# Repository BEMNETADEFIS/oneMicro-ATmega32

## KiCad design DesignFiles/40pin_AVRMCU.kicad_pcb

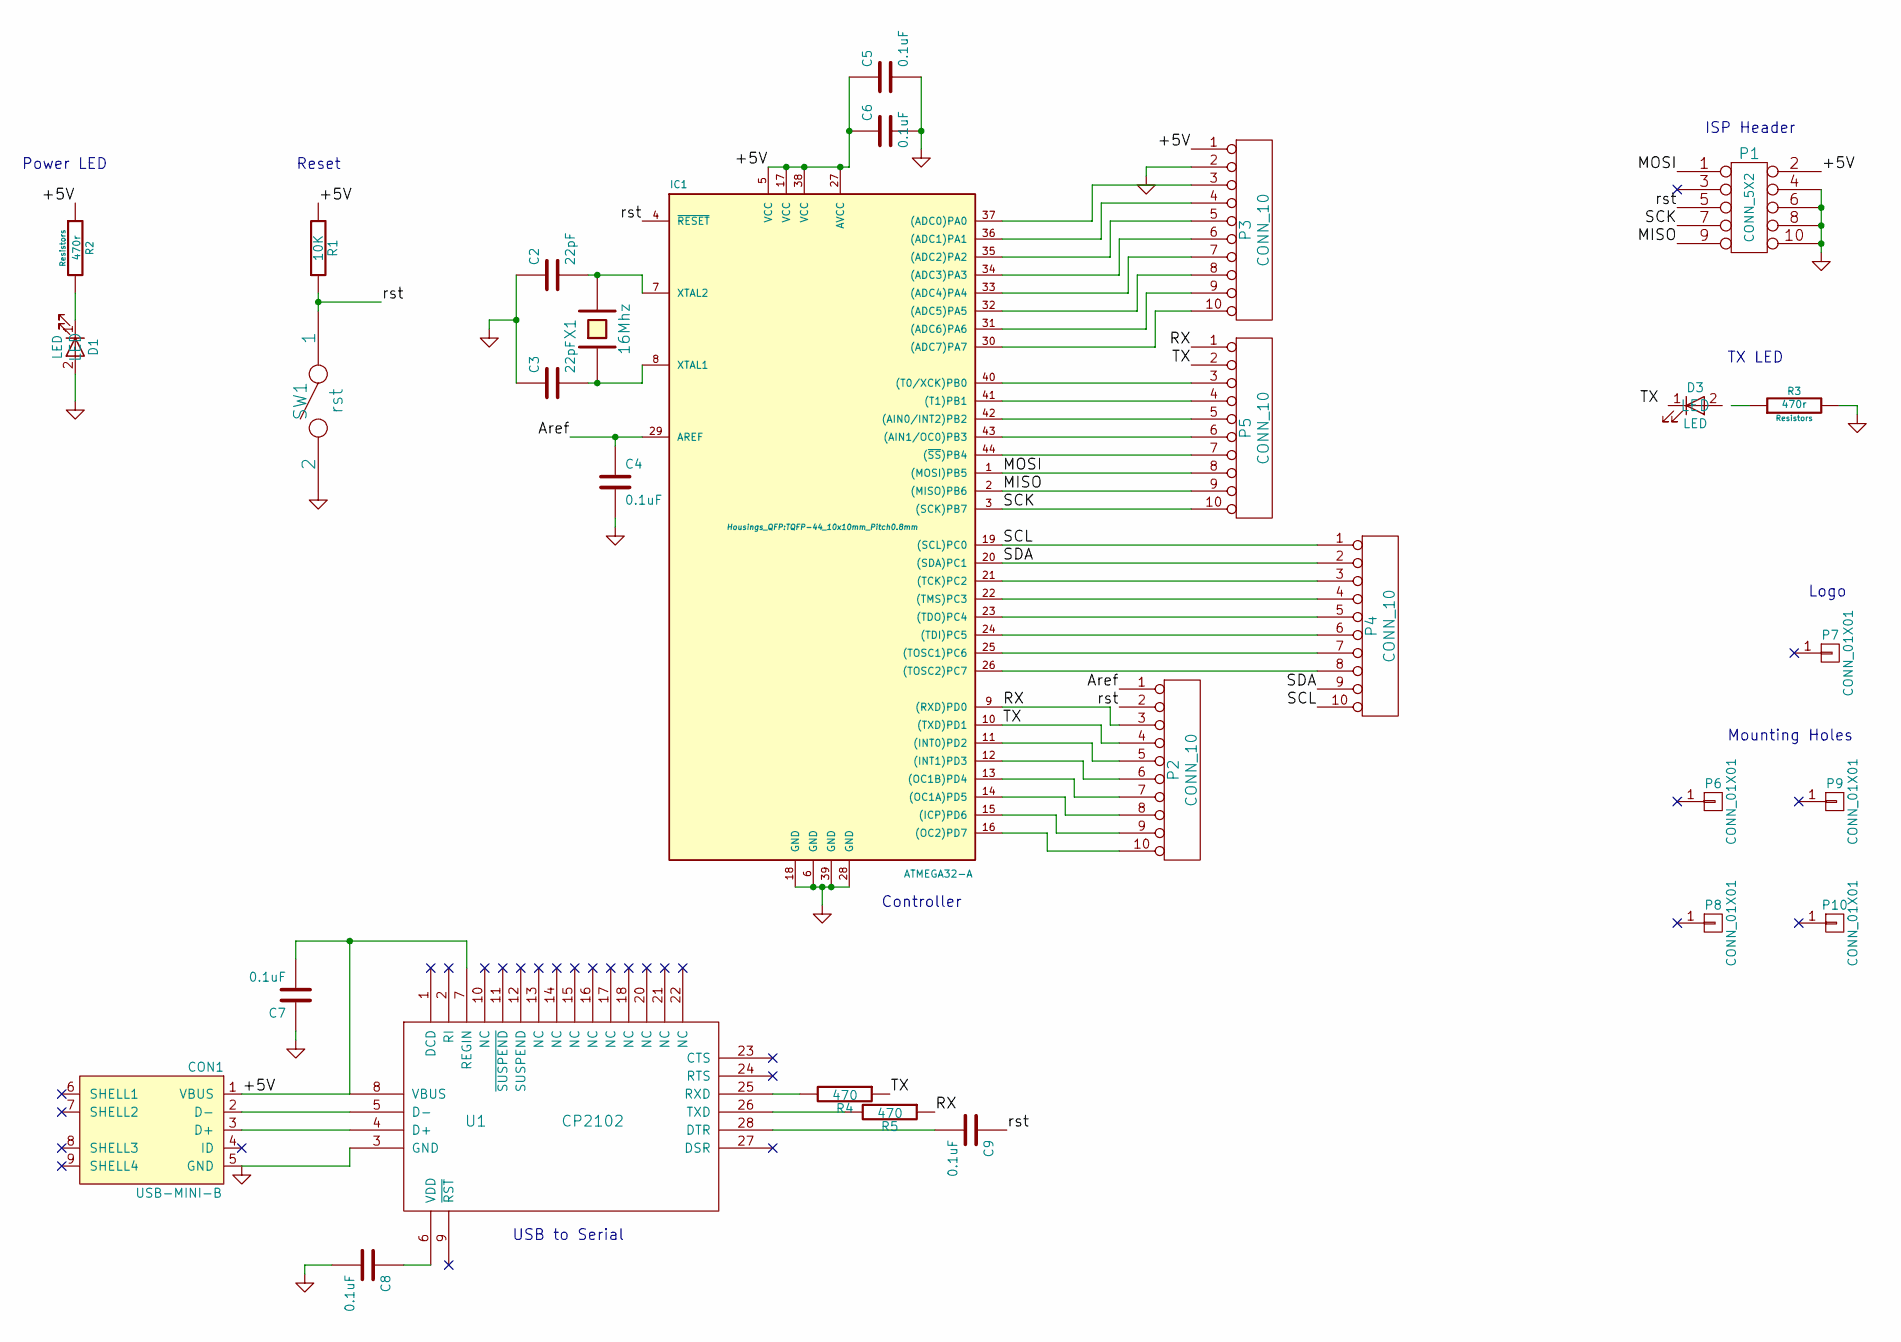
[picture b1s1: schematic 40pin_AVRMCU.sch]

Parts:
C2, C3: 22pF; C_0603_HandSoldering
C4, C5, C6, C7, C8, C9: 0.1uF; C_0603_HandSoldering
CON1: USB-MINI-B; USB_Micro-B_SMD_NEW_1
D1, D3: LED
IC1: ATMEGA32-A; TQFP-44_10x10mm_Pitch0.8mm
P1: CONN_5X2; Pin_Header_Straight_2x05_Pitch2.54mm
P2, P3, P4, P5: CONN_10; Pin_Header_Straight_1x10_Pitch2.54mm
P6, P8, P9, P10: CONN_01X01; 1pin
P7: CONN_01X01; Logo_8
R1: 10K; R_0603_HandSoldering
R2, R3: 470r; Resistors
R4, R5: 470; R_0603_HandSoldering
SW1: rst; SW_PUSH_SMALL_2pin_3D_xl_v1
U1: CP2102; cp2102_xl2
X1: 16Mhz; Crystal_HC18-U_Vertical

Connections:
/+5V: C5.1, C6.1, C7.2, CON1.1 (VBUS), IC1.5 (VCC), IC1.17 (VCC), IC1.27 (AVCC), IC1.38 (VCC), P1.2, P3.1, R1.2, R2.1, U1.7 (REGIN), U1.8 (VBUS)
/Aref: C4.1, IC1.29 (AREF), P2.1
/MISO: IC1.2 ((MISO)PB6), P1.9, P5.9
/MOSI: IC1.1 ((MOSI)PB5), P1.1, P5.8
/RX: IC1.9 ((RXD)PD0), P2.3, P5.1, R5.1
/SCK: IC1.3 ((SCK)PB7), P1.7, P5.10
/SCL: IC1.19 ((SCL)PC0), P4.1, P4.10
/SDA: IC1.20 ((SDA)PC1), P4.2, P4.9
/TX: D3.1 (K), IC1.10 ((TXD)PD1), P2.4, P5.2, R4.1
/rst: C9.1, IC1.4 (~RESET), P1.5, P2.2, R1.1, SW1.1
GND: C2.1, C3.1, C4.2, C5.2, C6.2, C7.1, C8.2, CON1.5 (GND), D1.2 (A), IC1.6 (GND), IC1.18 (GND), IC1.28 (GND), IC1.39 (GND), P1.4, P1.6, P1.8, P1.10, P3.2, R3.2, SW1.2, U1.3 (GND)
unnamed: C2.2, IC1.7 (XTAL2), X1.2
unnamed: C3.2, IC1.8 (XTAL1), X1.1
unnamed: C8.1, U1.6 (VDD)
unnamed: C9.2, U1.28 (DTR)
unnamed: CON1.2 (D-), U1.5 (D-)
unnamed: CON1.3 (D+), U1.4 (D+)
unnamed: D1.1 (K), R2.2
unnamed: D3.2 (A), R3.1
unnamed: IC1.11 ((INT0)PD2), P2.5
unnamed: IC1.12 ((INT1)PD3), P2.6
unnamed: IC1.13 ((OC1B)PD4), P2.7
unnamed: IC1.14 ((OC1A)PD5), P2.8
unnamed: IC1.15 ((ICP)PD6), P2.9
unnamed: IC1.16 ((OC2)PD7), P2.10
unnamed: IC1.21 ((TCK)PC2), P4.3
unnamed: IC1.22 ((TMS)PC3), P4.4
unnamed: IC1.23 ((TDO)PC4), P4.5
unnamed: IC1.24 ((TDI)PC5), P4.6
unnamed: IC1.25 ((TOSC1)PC6), P4.7
unnamed: IC1.26 ((TOSC2)PC7), P4.8
unnamed: IC1.30 ((ADC7)PA7), P3.10
unnamed: IC1.31 ((ADC6)PA6), P3.9
unnamed: IC1.32 ((ADC5)PA5), P3.8
unnamed: IC1.33 ((ADC4)PA4), P3.7
unnamed: IC1.34 ((ADC3)PA3), P3.6
unnamed: IC1.35 ((ADC2)PA2), P3.5
unnamed: IC1.36 ((ADC1)PA1), P3.4
unnamed: IC1.37 ((ADC0)PA0), P3.3
unnamed: IC1.40 ((T0/XCK)PB0), P5.3
unnamed: IC1.41 ((T1)PB1), P5.4
unnamed: IC1.42 ((AIN0/INT2)PB2), P5.5
unnamed: IC1.43 ((AIN1/OC0)PB3), P5.6
unnamed: IC1.44 ((~SS~)PB4), P5.7
unnamed: R4.2, U1.25 (RXD)
unnamed: R5.2, U1.26 (TXD)

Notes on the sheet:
ISP Header
Reset
TX LED
USB to Serial
Power LED
Logo
Mounting Holes
Controller

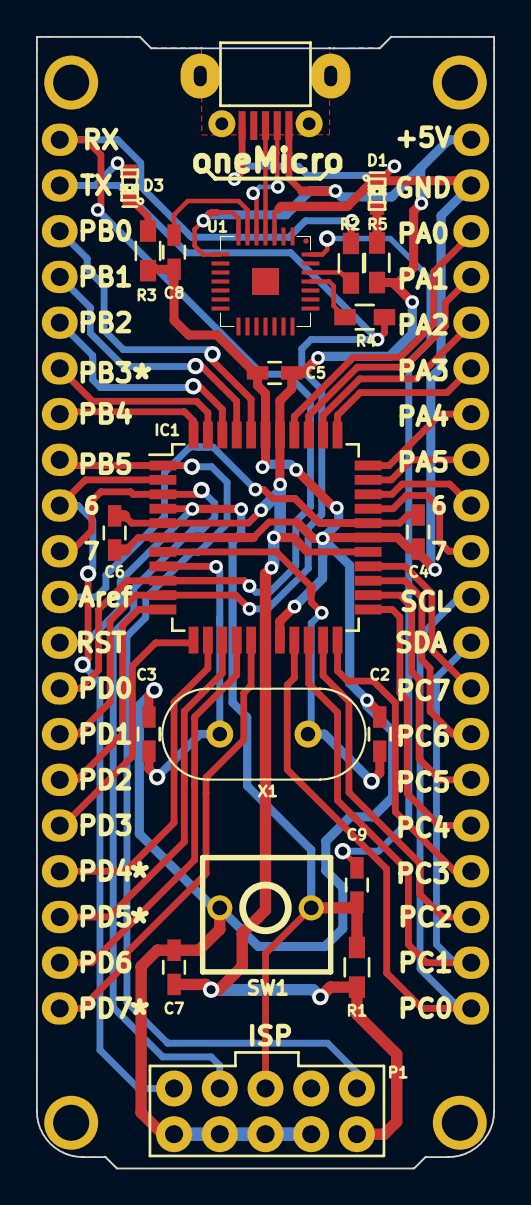
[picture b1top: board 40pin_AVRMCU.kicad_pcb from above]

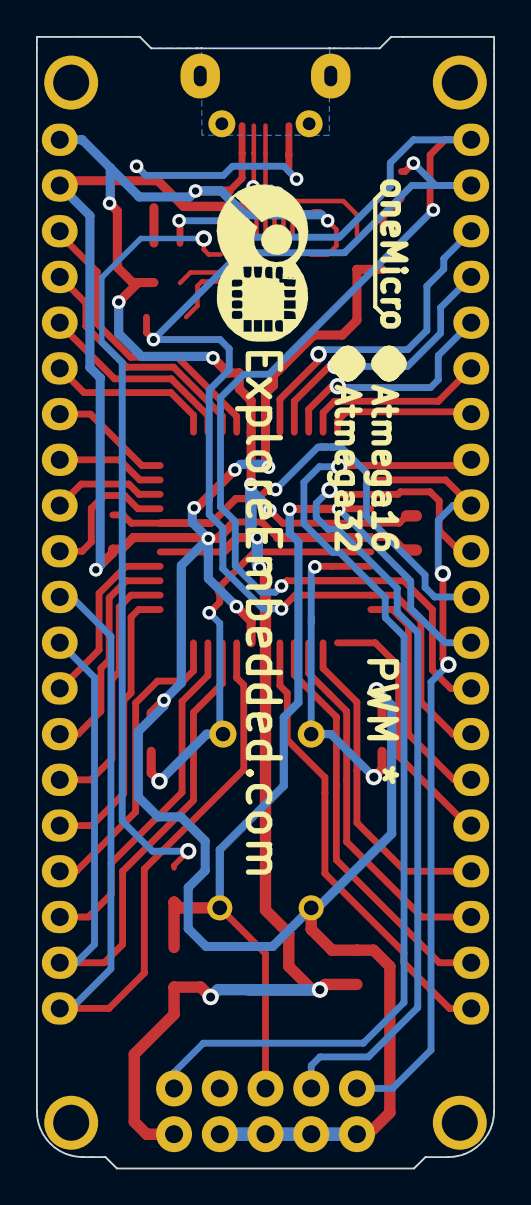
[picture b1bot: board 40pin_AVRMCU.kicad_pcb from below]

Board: 2 copper layers, 25.4 x 62.9 mm, 30 parts (5 on the bottom side), 46 nets.

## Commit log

2016-07-28 Added Design Files
2016-07-29 Updated designs
2016-07-30 Routing
2016-08-29 BOM Generated
2016-08-30 Added Sample Code for Atmega32
    Added Sample Code for Atmega32
2016-09-08 BOM updated
2016-09-20 added bootloader files
2017-03-17 Changes done
2017-09-09 Schematic PDF added
